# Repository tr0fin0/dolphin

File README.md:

# dolphin
Firmware for `dolphin` board, an ESP32-S3 based sumo robot controller.

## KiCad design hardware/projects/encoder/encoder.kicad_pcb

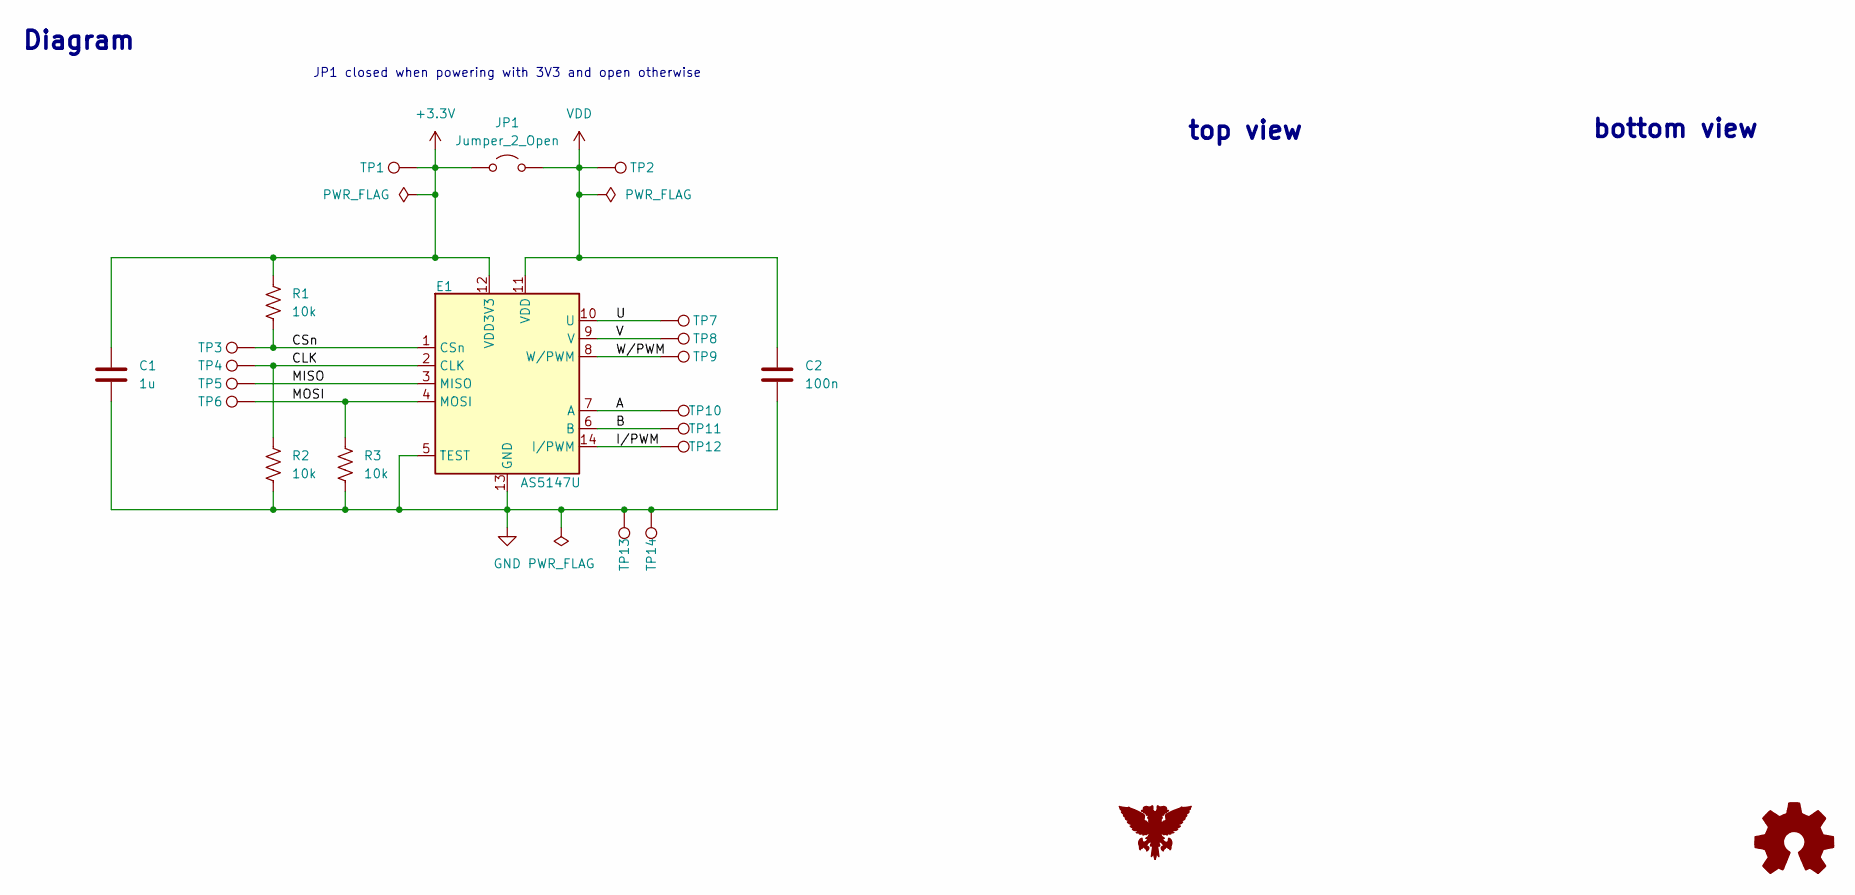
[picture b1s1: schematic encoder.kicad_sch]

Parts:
C1: 1u; C_0805_2012Metric_Pad1.18x1.45mm_HandSolder
C2: 100n; C_0805_2012Metric_Pad1.18x1.45mm_HandSolder
E1: AS5147U; Encoder_AS5147U
JP1: Jumper_2_Open; SolderJumper-2_P1.3mm_Open_TrianglePad1.0x1.5mm
R1, R2, R3: 10k; R_0805_2012Metric_Pad1.20x1.40mm_HandSolder
TP1, TP2, TP3, TP4, TP5, TP6, TP7, TP8, TP9, TP10, TP11, TP12, TP13, TP14: TestPoint; TestPoint_Pad_D1.0mm

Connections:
+3.3V: C1.2, E1.12 (VDD3V3), JP1.1 (A), R1.1, TP1.1 (1_1)
/A: E1.7 (A), TP10.1 (1_1)
/B: E1.6 (B), TP11.1 (1_1)
/CLK: E1.2 (CLK), R2.1, TP4.1 (1_1)
/CSn: E1.1 (CSn), R1.2, TP3.1 (1_1)
/I/PWM: E1.14 (I/PWM), TP12.1 (1_1)
/MISO: E1.3 (MISO), TP5.1 (1_1)
/MOSI: E1.4 (MOSI), R3.1, TP6.1 (1_1)
/U: E1.10 (U), TP7.1 (1_1)
/V: E1.9 (V), TP8.1 (1_1)
/W/PWM: E1.8 (W/PWM), TP9.1 (1_1)
GND: C1.1, C2.1, E1.5 (TEST), E1.13 (GND), R2.2, R3.2, TP13.1 (1_1), TP14.1 (1_1)
VDD: C2.2, E1.11 (VDD), JP1.2 (B), TP2.1 (1_1)

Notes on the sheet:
Diagram
JP1 closed when powering with 3V3 and open otherwise
top view
bottom view

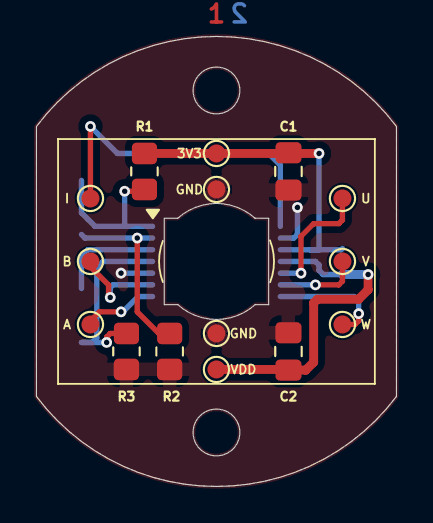
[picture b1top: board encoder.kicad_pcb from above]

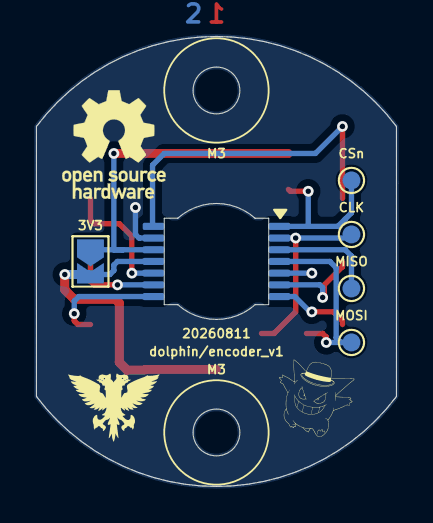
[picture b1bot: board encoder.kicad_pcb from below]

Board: 2 copper layers, 20.0 x 25.0 mm, 21 parts (5 on the bottom side), 13 nets.

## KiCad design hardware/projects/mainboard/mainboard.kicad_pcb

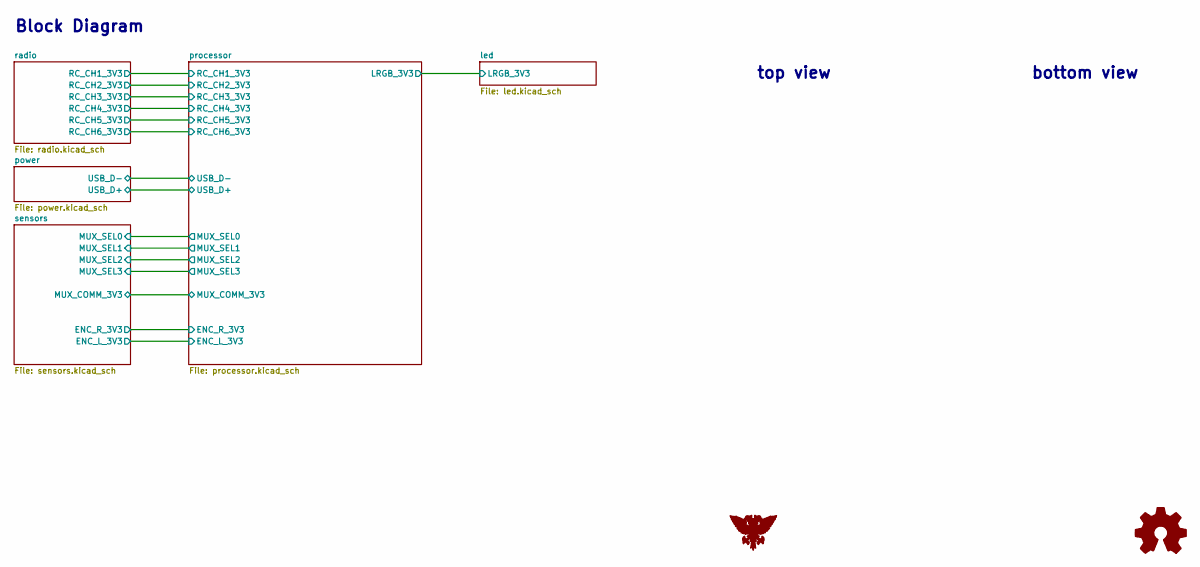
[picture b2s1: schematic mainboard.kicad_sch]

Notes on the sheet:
top view
bottom view
Block Diagram

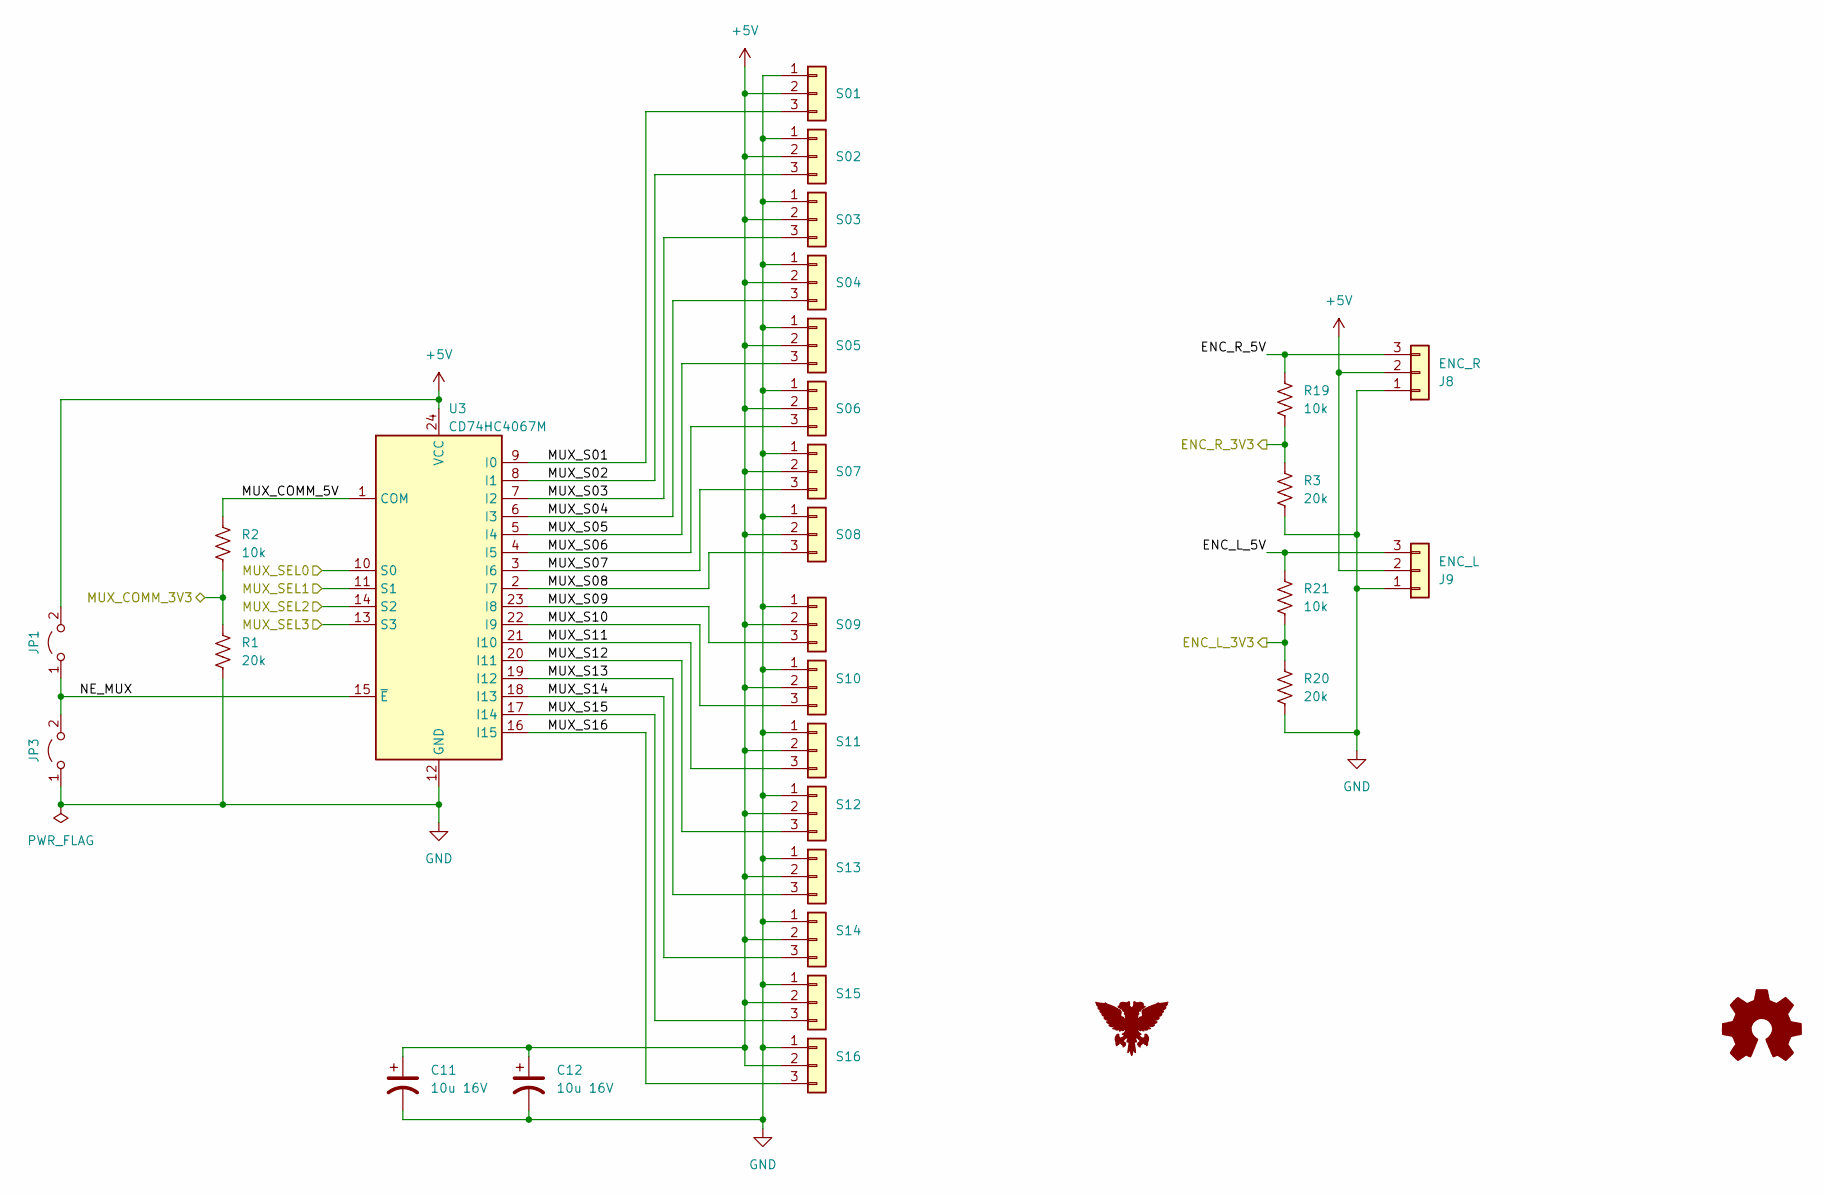
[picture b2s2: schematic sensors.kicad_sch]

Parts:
C11, C12: 10u 16V; CP_Radial_D5.0mm_P2.00mm
J8: ENC_R; Connector_JST_ZH_B3B-ZR_1x03_P1.50mm_Vertical
J9: ENC_L; Connector_JST_ZH_B3B-ZR_1x03_P1.50mm_Vertical
JP1, JP3: Jumper_2_Open; SolderJumper-2_P1.3mm_Open_TrianglePad1.0x1.5mm
R1, R3, R20: 20k; R_0805_2012Metric_Pad1.20x1.40mm_HandSolder
R2, R19, R21: 10k; R_0805_2012Metric_Pad1.20x1.40mm_HandSolder
S01, S02, S03, S04, S05, S06, S07, S08, S09, S10, S11, S12, S13, S14, S15, S16: Conn_01x03; Connector_JST_ZH_B3B-ZR_1x03_P1.50mm_Vertical
U3: CD74HC4067M; SOIC-24W_7.5x15.4mm_P1.27mm

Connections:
+5V: C11.1, C12.1, J8.2, J9.2, JP1.2 (B), S01.2, S02.2, S03.2, S04.2, S05.2, S06.2, S07.2, S08.2, S09.2, S10.2, S11.2, S12.2, S13.2, S14.2, S15.2, S16.2, U3.24 (VCC); also elsewhere on the board
/processor/ENC_L_3V3: R20.1, R21.1; also elsewhere on the board
/processor/ENC_R_3V3: R3.1, R19.1; also elsewhere on the board
/processor/MUX_COMM_3V3: R1.1, R2.1; also elsewhere on the board
/processor/MUX_SEL0: U3.10 (S0); also elsewhere on the board
/processor/MUX_SEL1: U3.11 (S1); also elsewhere on the board
/processor/MUX_SEL2: U3.14 (S2); also elsewhere on the board
/processor/MUX_SEL3: U3.13 (S3); also elsewhere on the board
/sensors/ENC_L_5V: J9.3, R21.2
/sensors/ENC_R_5V: J8.3, R19.2
/sensors/MUX_COMM_5V: R2.2, U3.1 (COM)
/sensors/MUX_S01: S01.3, U3.9 (I0)
/sensors/MUX_S02: S02.3, U3.8 (I1)
/sensors/MUX_S03: S03.3, U3.7 (I2)
/sensors/MUX_S04: S04.3, U3.6 (I3)
/sensors/MUX_S05: S05.3, U3.5 (I4)
/sensors/MUX_S06: S06.3, U3.4 (I5)
/sensors/MUX_S07: S07.3, U3.3 (I6)
/sensors/MUX_S08: S08.3, U3.2 (I7)
/sensors/MUX_S09: S09.3, U3.23 (I8)
/sensors/MUX_S10: S10.3, U3.22 (I9)
/sensors/MUX_S11: S11.3, U3.21 (I10)
/sensors/MUX_S12: S12.3, U3.20 (I11)
/sensors/MUX_S13: S13.3, U3.19 (I12)
/sensors/MUX_S14: S14.3, U3.18 (I13)
/sensors/MUX_S15: S15.3, U3.17 (I14)
/sensors/MUX_S16: S16.3, U3.16 (I15)
/sensors/NE_MUX: JP1.1 (A), JP3.2 (B), U3.15 (~E)
GND: C11.2, C12.2, J8.1, J9.1, JP3.1 (A), R1.2, R3.2, R20.2, S01.1, S02.1, S03.1, S04.1, S05.1, S06.1, S07.1, S08.1, S09.1, S10.1, S11.1, S12.1, S13.1, S14.1, S15.1, S16.1, U3.12 (GND); also elsewhere on the board

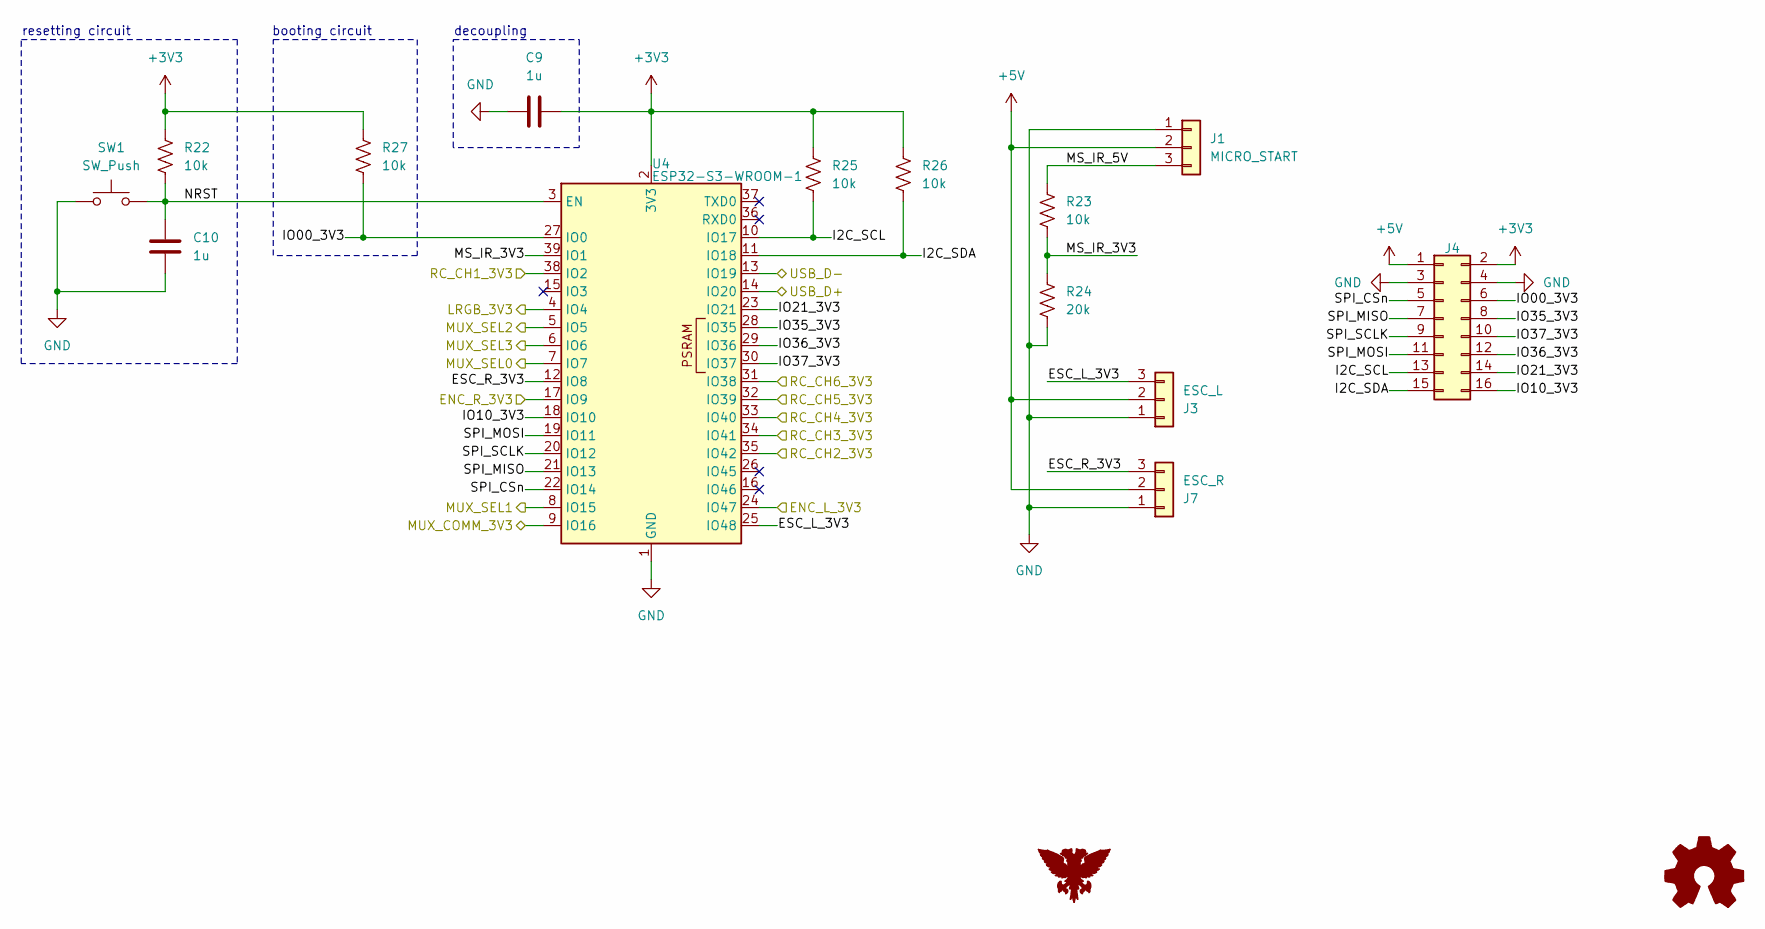
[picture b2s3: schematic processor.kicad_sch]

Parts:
C9, C10: 1u; C_0805_2012Metric_Pad1.18x1.45mm_HandSolder
J1: MICRO_START; Connector_JST_ZH_B3B-ZR_1x03_P1.50mm_Vertical
J3: ESC_L; PinSocket_1x03_P2.54mm_Vertical
J4: Conn_02x08_Odd_Even; PinSocket_2x08_P2.54mm_Vertical
J7: ESC_R; PinSocket_1x03_P2.54mm_Vertical
R22, R23, R25, R26, R27: 10k; R_0805_2012Metric_Pad1.20x1.40mm_HandSolder
R24: 20k; R_0805_2012Metric_Pad1.20x1.40mm_HandSolder
SW1: SW_Push; SW_SPST_PTS810
U4: ESP32-S3-WROOM-1

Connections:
+3V3: C9.2, J4.2, R22.1, R25.1, R26.1, R27.2, U4.2 (3V3); also elsewhere on the board
+5V: J1.2, J3.2, J4.1, J7.2; also elsewhere on the board
/led/LRGB_3V3: U4.4 (IO4); also elsewhere on the board
/power/USB_D+: U4.14 (IO20); also elsewhere on the board
/power/USB_D-: U4.13 (IO19); also elsewhere on the board
/processor/ENC_L_3V3: U4.24 (IO47); also elsewhere on the board
/processor/ENC_R_3V3: U4.17 (IO9); also elsewhere on the board
/processor/ESC_L_3V3: J3.3, U4.25 (IO48)
/processor/ESC_R_3V3: J7.3, U4.12 (IO8)
/processor/I2C_SCL: J4.13, R25.2, U4.10 (IO17)
/processor/I2C_SDA: J4.15, R26.2, U4.11 (IO18)
/processor/IO00_3V3: J4.6, R27.1, U4.27 (IO0)
/processor/IO10_3V3: J4.16, U4.18 (IO10)
/processor/IO21_3V3: J4.14, U4.23 (IO21)
/processor/IO35_3V3: J4.8, U4.28 (IO35)
/processor/IO36_3V3: J4.12, U4.29 (IO36)
/processor/IO37_3V3: J4.10, U4.30 (IO37)
/processor/MS_IR_3V3: R23.2, R24.1, U4.39 (IO1)
/processor/MS_IR_5V: J1.3, R23.1
/processor/MUX_COMM_3V3: U4.9 (IO16); also elsewhere on the board
/processor/MUX_SEL0: U4.7 (IO7); also elsewhere on the board
/processor/MUX_SEL1: U4.8 (IO15); also elsewhere on the board
/processor/MUX_SEL2: U4.5 (IO5); also elsewhere on the board
/processor/MUX_SEL3: U4.6 (IO6); also elsewhere on the board
/processor/NRST: C10.1, R22.2, SW1.2, U4.3 (EN)
/processor/RC_CH1_3V3: U4.38 (IO2); also elsewhere on the board
/processor/RC_CH2_3V3: U4.35 (IO42); also elsewhere on the board
/processor/RC_CH3_3V3: U4.34 (IO41); also elsewhere on the board
/processor/RC_CH4_3V3: U4.33 (IO40); also elsewhere on the board
/processor/RC_CH5_3V3: U4.32 (IO39); also elsewhere on the board
/processor/RC_CH6_3V3: U4.31 (IO38); also elsewhere on the board
/processor/SPI_CSn: J4.5, U4.22 (IO14)
/processor/SPI_MISO: J4.7, U4.21 (IO13)
/processor/SPI_MOSI: J4.11, U4.19 (IO11)
/processor/SPI_SCLK: J4.9, U4.20 (IO12)
GND: C9.1, C10.2, J1.1, J3.1, J4.3, J4.4, J7.1, R24.2, SW1.1, U4.1 (GND), U4.40 (GND), U4.41 (GND); also elsewhere on the board

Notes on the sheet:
resetting circuit
decoupling
booting circuit

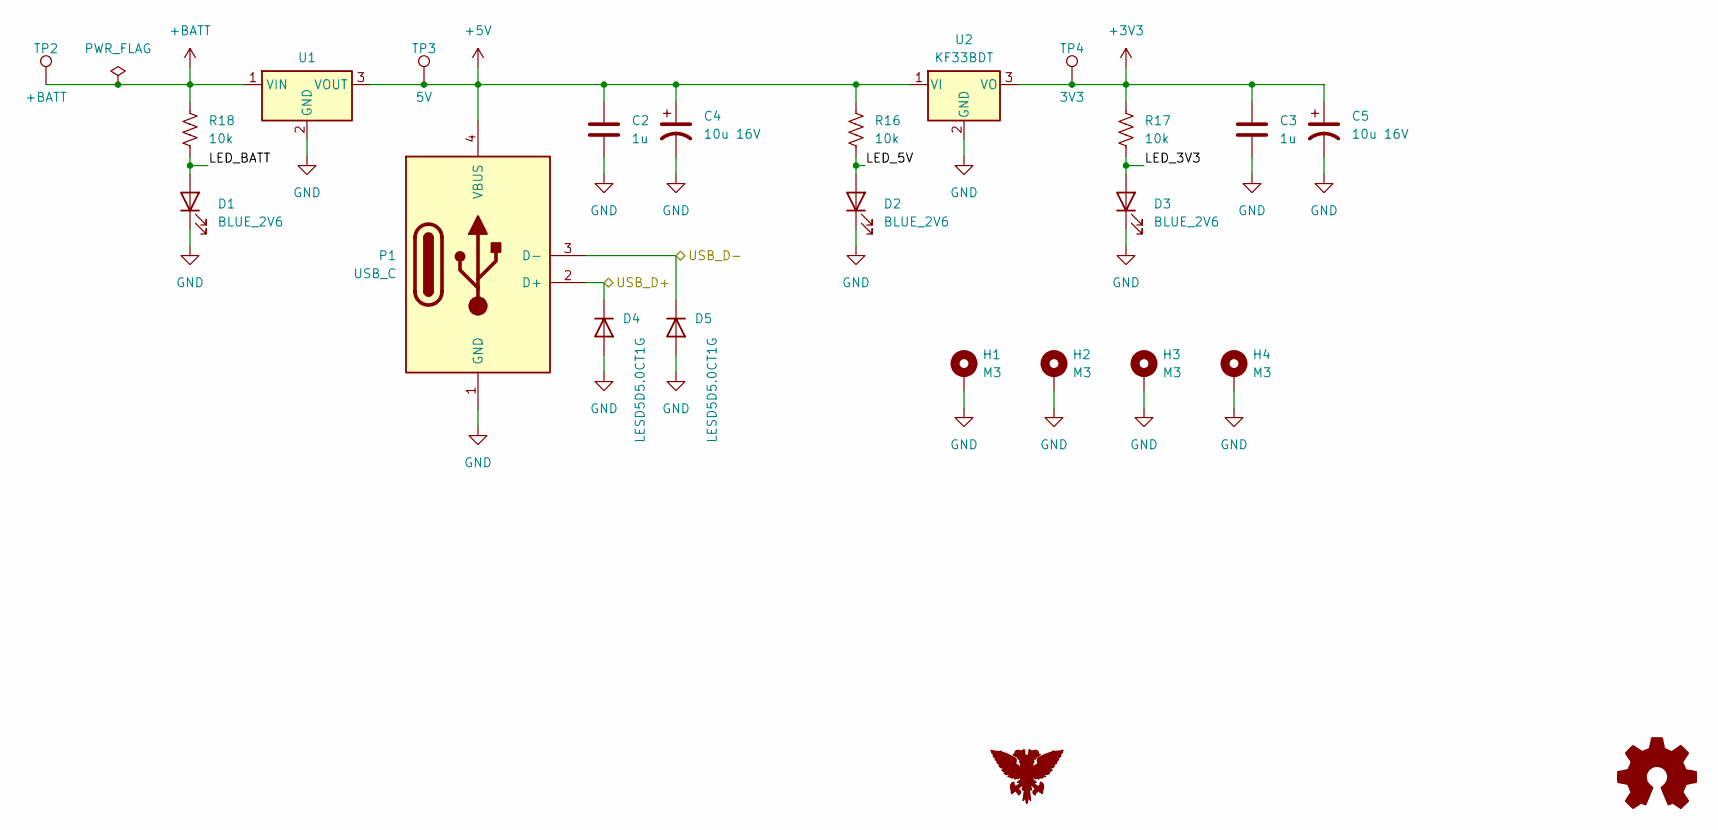
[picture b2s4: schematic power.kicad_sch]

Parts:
C2, C3: 1u; C_0805_2012Metric_Pad1.18x1.45mm_HandSolder
C4, C5: 10u 16V; CP_Radial_D5.0mm_P2.00mm
D1, D2, D3: BLUE_2V6; LED_0805_2012Metric_Pad1.15x1.40mm_HandSolder
D4, D5: LESD5D5.0CT1G; D_0805_2012Metric_Pad1.15x1.40mm_HandSolder
H1, H2, H3, H4: M3; MountingHole_3.2mm_M3_Pad_Via
P1: USB_C; Connector_USB-C
R16, R17, R18: 10k; R_0805_2012Metric_Pad1.20x1.40mm_HandSolder
TP2: +BATT; TestPoint_Pad_D1.0mm
TP3: 5V; TestPoint_Pad_D1.0mm
TP4: 3V3; TestPoint_Pad_D1.0mm
U1: Regulator_DC-DC_MINI-360
U2: KF33BDT; Regulator_KF33BD-TR

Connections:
+3V3: C3.1, C5.1, R17.1, TP4.1 (1_1), U2.3 (VO); also elsewhere on the board
+5V: C2.1, C4.1, P1.4 (VBUS), R16.1, TP3.1 (1_1), U1.3 (VOUT), U2.1 (VI); also elsewhere on the board
+BATT: R18.1, TP2.1 (1_1), U1.1 (VIN)
/power/LED_3V3: D3.2 (A), R17.2
/power/LED_5V: D2.2 (A), R16.2
/power/LED_BATT: D1.2 (A), R18.2
/power/USB_D+: D4.1 (K), P1.2 (D+); also elsewhere on the board
/power/USB_D-: D5.1 (K), P1.3 (D-); also elsewhere on the board
GND: C2.2, C3.2, C4.2, C5.2, D1.1 (K), D2.1 (K), D3.1 (K), D4.2 (A), D5.2 (A), H1.1 (1_1), H2.1 (1_1), H3.1 (1_1), H4.1 (1_1), P1.1 (GND), U1.2 (GND), U2.2 (GND); also elsewhere on the board

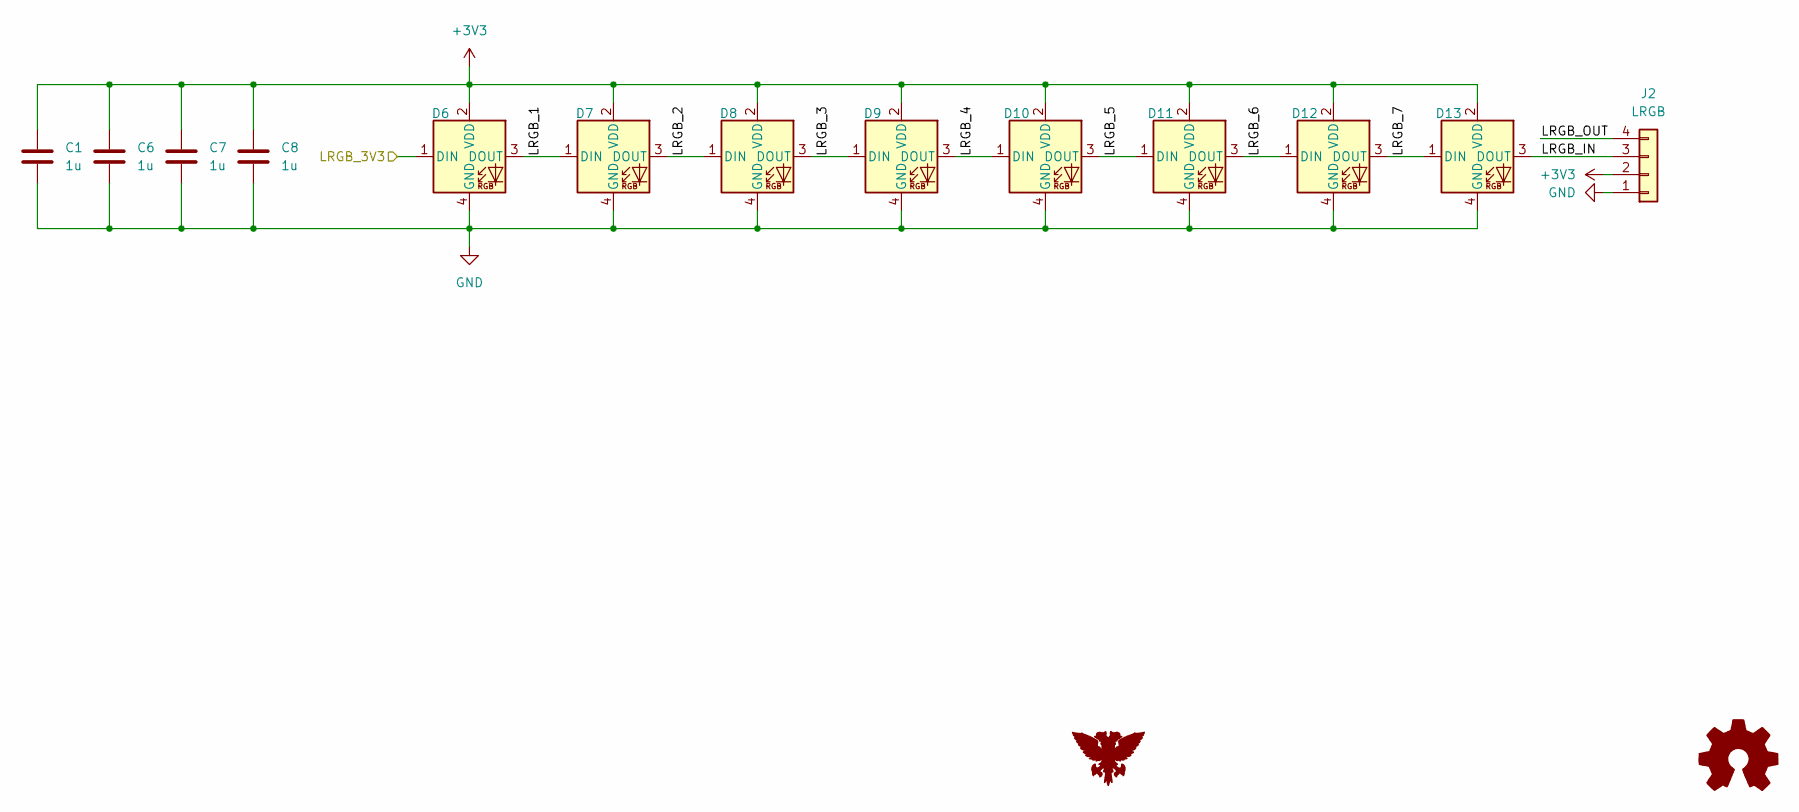
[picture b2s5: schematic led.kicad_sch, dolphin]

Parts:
C1, C6, C7, C8: 1u; C_0805_2012Metric_Pad1.18x1.45mm_HandSolder
D6, D7, D8, D9, D10, D11, D12, D13: WS2812B-4020-G1; LED_WS2812B-4020
J2: LRGB; Connector_JST_ZH_B4B-ZR_1x04_P1.50mm_Vertical

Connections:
+3V3: C1.1, C6.1, C7.1, C8.1, D6.2 (VDD), D7.2 (VDD), D8.2 (VDD), D9.2 (VDD), D10.2 (VDD), D11.2 (VDD), D12.2 (VDD), D13.2 (VDD), J2.2; also elsewhere on the board
/led/LRGB_1: D6.3 (DOUT), D7.1 (DIN)
/led/LRGB_2: D7.3 (DOUT), D8.1 (DIN)
/led/LRGB_3: D8.3 (DOUT), D9.1 (DIN)
/led/LRGB_3V3: D6.1 (DIN); also elsewhere on the board
/led/LRGB_4: D9.3 (DOUT), D10.1 (DIN)
/led/LRGB_5: D10.3 (DOUT), D11.1 (DIN)
/led/LRGB_6: D11.3 (DOUT), D12.1 (DIN)
/led/LRGB_7: D12.3 (DOUT), D13.1 (DIN)
/led/LRGB_IN: D13.3 (DOUT), J2.3
/led/LRGB_OUT: J2.4
GND: C1.2, C6.2, C7.2, C8.2, D6.4 (GND), D7.4 (GND), D8.4 (GND), D9.4 (GND), D10.4 (GND), D11.4 (GND), D12.4 (GND), D13.4 (GND), J2.1; also elsewhere on the board

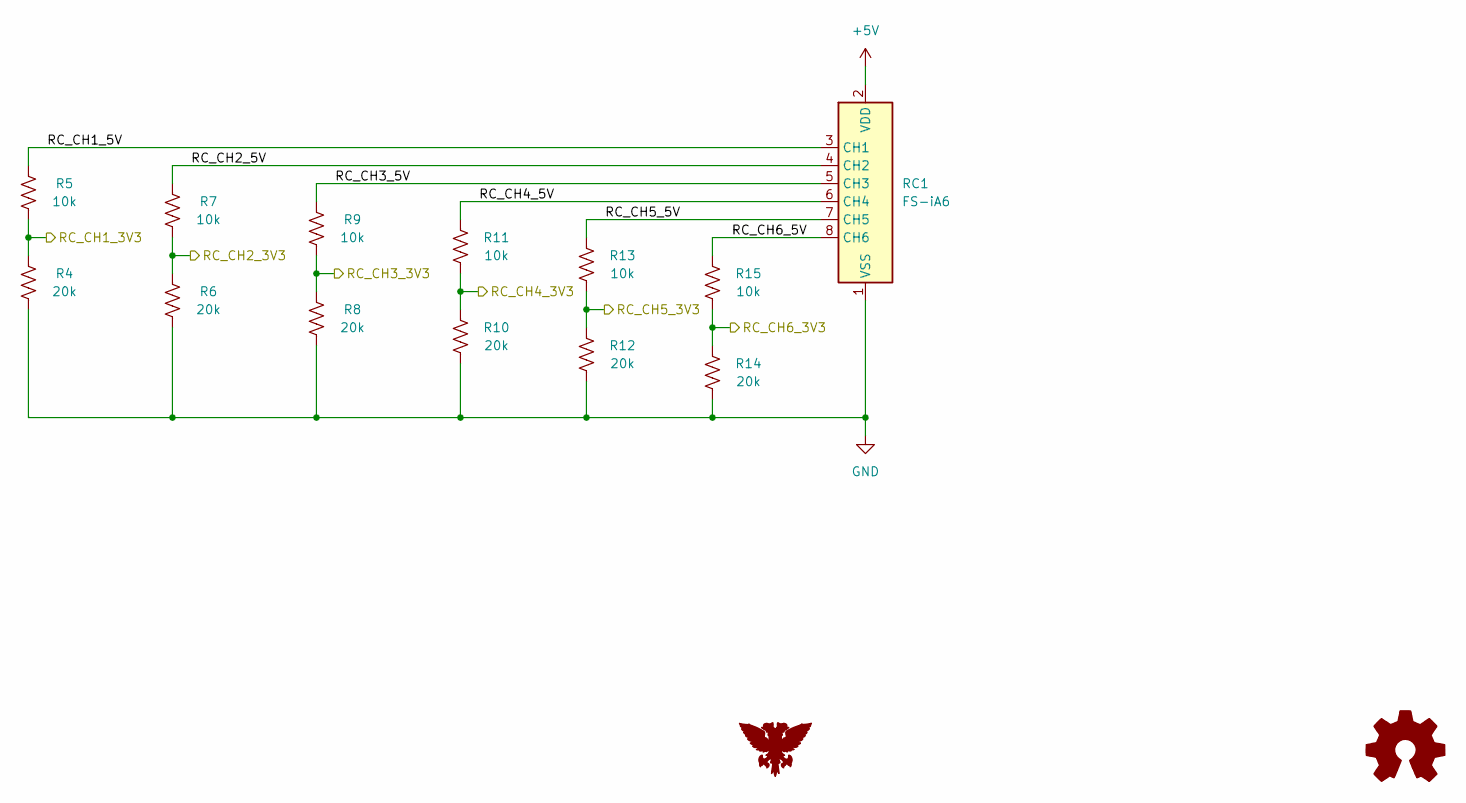
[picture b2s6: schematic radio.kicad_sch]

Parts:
R4, R6, R8, R10, R12, R14: 20k; R_0805_2012Metric_Pad1.20x1.40mm_HandSolder
R5, R7, R9, R11, R13, R15: 10k; R_0805_2012Metric_Pad1.20x1.40mm_HandSolder
RC1: FS-iA6; Receiver_FS-iA6

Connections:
+5V: RC1.2 (VDD); also elsewhere on the board
/processor/RC_CH1_3V3: R4.2, R5.1; also elsewhere on the board
/processor/RC_CH2_3V3: R6.2, R7.1; also elsewhere on the board
/processor/RC_CH3_3V3: R8.2, R9.1; also elsewhere on the board
/processor/RC_CH4_3V3: R10.2, R11.1; also elsewhere on the board
/processor/RC_CH5_3V3: R12.2, R13.1; also elsewhere on the board
/processor/RC_CH6_3V3: R14.2, R15.1; also elsewhere on the board
/radio/RC_CH1_5V: R5.2, RC1.3 (CH1)
/radio/RC_CH2_5V: R7.2, RC1.4 (CH2)
/radio/RC_CH3_5V: R9.2, RC1.5 (CH3)
/radio/RC_CH4_5V: R11.2, RC1.6 (CH4)
/radio/RC_CH5_5V: R13.2, RC1.7 (CH5)
/radio/RC_CH6_5V: R15.2, RC1.8 (CH6)
GND: R4.1, R6.1, R8.1, R10.1, R12.1, R14.1, RC1.1 (VSS); also elsewhere on the board

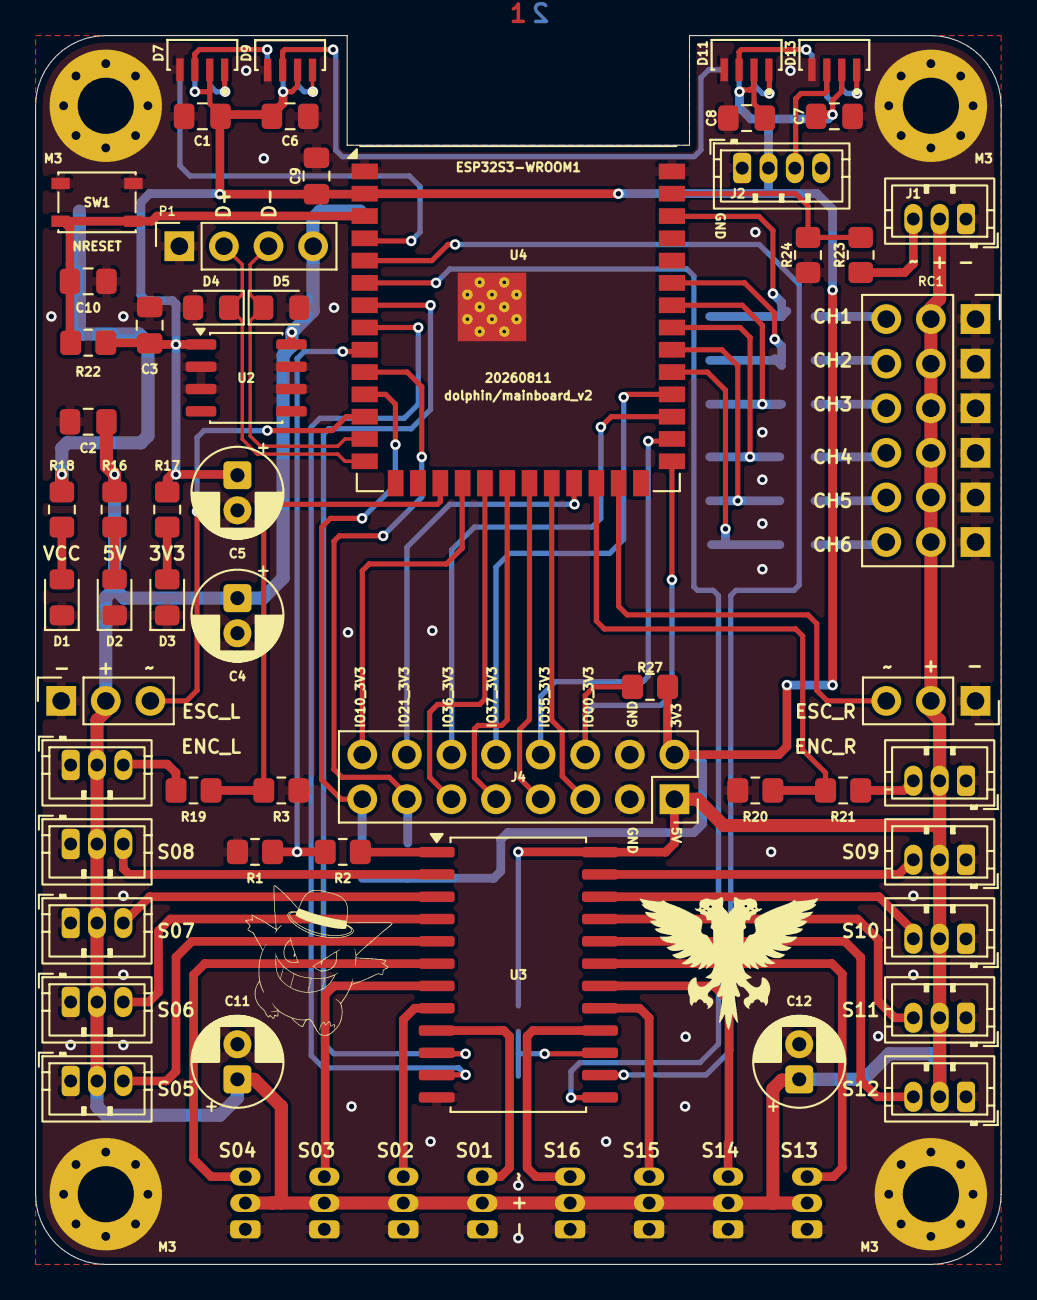
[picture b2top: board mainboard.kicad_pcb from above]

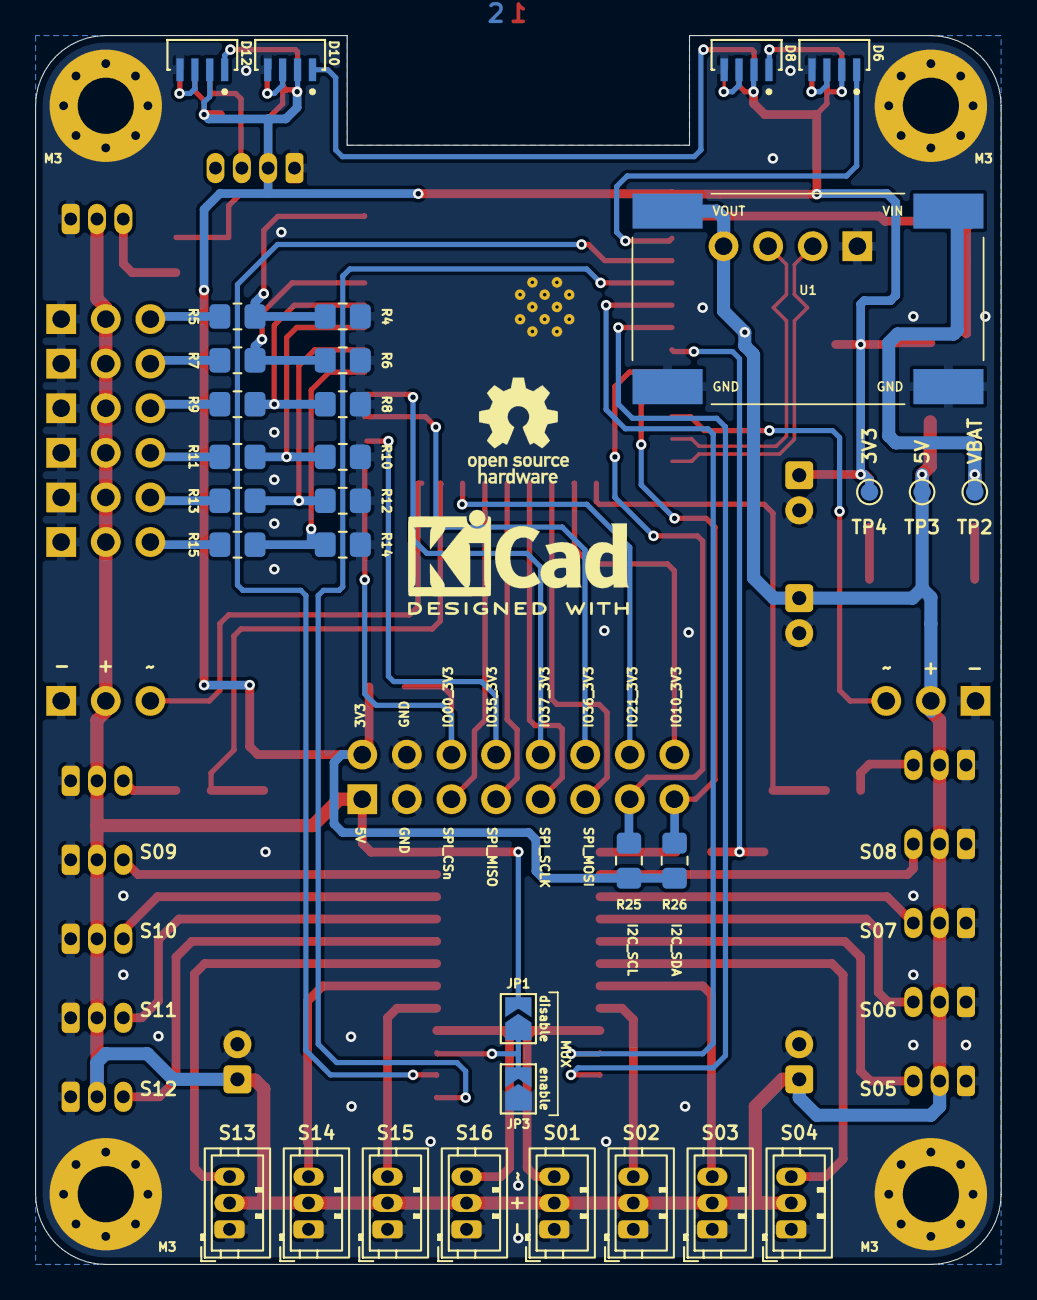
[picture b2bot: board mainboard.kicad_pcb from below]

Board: 2 copper layers, 55.0 x 70.0 mm, 91 parts (32 on the bottom side), 74 nets.

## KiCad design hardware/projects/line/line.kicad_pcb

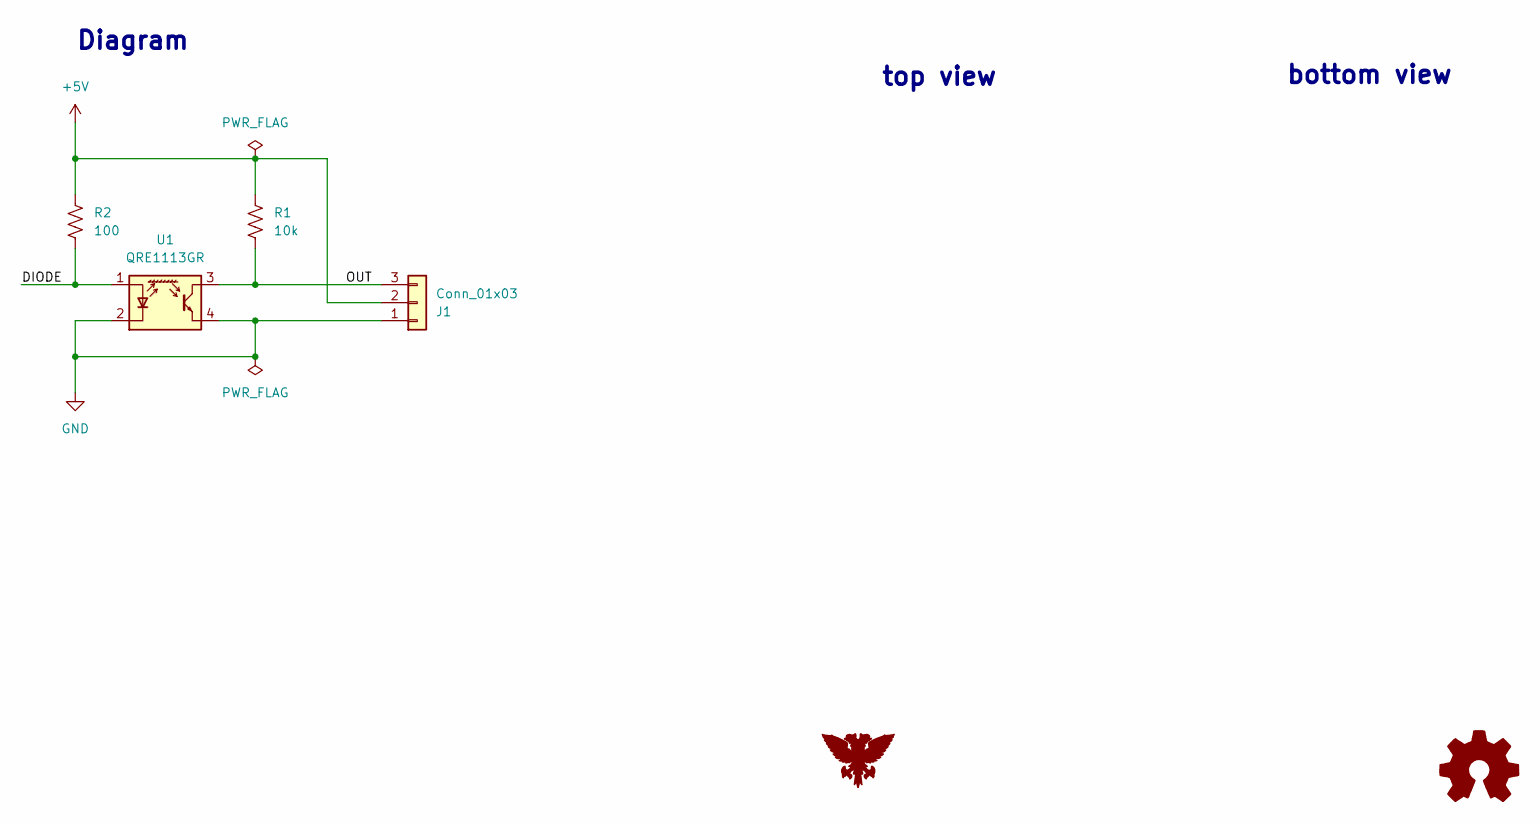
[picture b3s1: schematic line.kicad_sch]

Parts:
J1: Conn_01x03; PinHeader_1x03_P2.54mm_Vertical
R1: 10k; R_0805_2012Metric_Pad1.20x1.40mm_HandSolder
R2: 100; R_0805_2012Metric_Pad1.20x1.40mm_HandSolder
U1: QRE1113GR; OnSemi_CASE100CY

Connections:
+5V: J1.2, R1.1, R2.1
/DIODE: R2.2, U1.1 (A)
/OUT: J1.3, R1.2, U1.3
GND: J1.1, U1.2 (K), U1.4

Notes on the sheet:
bottom view
top view
Diagram

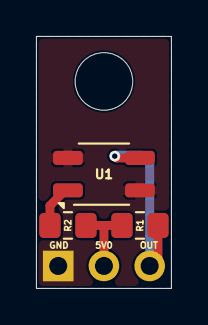
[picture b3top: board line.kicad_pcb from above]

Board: 2 copper layers, 7.5 x 14.0 mm, 4 parts (0 on the bottom side), 4 nets.

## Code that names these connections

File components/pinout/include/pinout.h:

/**
 * @file pinout.h
 * @brief Mainboard pinout.
 *
 * @author Guilherme Nunes Trofino
 * @date 2026-04-26
 */

#pragma once

#include "config.h"
#include <stdint.h>

/**
 * @brief Physical connection on the mainboard board.
 */
typedef enum pin {
#ifdef CONFIG_MAINBOARD_V2
    PIN_ENC_L = 47,         /**< ``GPIO 47`` : @ref ENCODER_L connection. */
    PIN_ENC_R = 9,          /**< ``GPIO 09`` : @ref ENCODER_R connection. */
    PIN_ESC_L = 48,         /**< ``GPIO 48`` : @ref ESC_L connection. */
    PIN_ESC_R = 8,          /**< ``GPIO 08`` : @ref ESC_R connection. */
    PIN_I2C_SCL = 17,       /**< ``GPIO 17`` : I2C clock line connection. */
    PIN_I2C_SDA = 18,       /**< ``GPIO 18`` : I2C data line connection. */
    PIN_IO00 = 0,           /**< ``GPIO 00`` : actively low, enables ESP32 boot mode. */
    PIN_IO10 = 10,          /**< ``GPIO 10`` : spare connection. */
    PIN_IO21 = 21,          /**< ``GPIO 21`` : spare connection. */
    PIN_IO35 = 35,          /**< ``GPIO 35`` : spare connection. */
    PIN_IO36 = 36,          /**< ``GPIO 36`` : spare connection. */
    PIN_IO37 = 37,          /**< ``GPIO 37`` : spare connection. */
    PIN_IRR = 1,            /**< ``GPIO 01`` : @ref ir_t infrared receiver connection. */
    PIN_LRGB = 4,           /**< ``GPIO 04`` : @ref led_array_t pin connection. */
    PIN_MUX_COMMON = 16,    /**< ``GPIO 16`` : @ref mux_t common pin connection. */
    PIN_MUX_ADDR0 = 7,      /**< ``GPIO 07`` : @ref mux_t address pin 0 connection. */
    PIN_MUX_ADDR1 = 15,     /**< ``GPIO 15`` : @ref mux_t address pin 1 connection. */
    PIN_MUX_ADDR2 = 5,      /**< ``GPIO 05`` : @ref mux_t address pin 2 connection. */
    PIN_MUX_ADDR3 = 6,      /**< ``GPIO 06`` : @ref mux_t address pin 3 connection. */
    PIN_RC_CH1 = 2,         /**< ``GPIO 02`` : @ref RADIO_CHANNEL_1 connection. */
    PIN_RC_CH2 = 42,        /**< ``GPIO 42`` : @ref RADIO_CHANNEL_2 connection. */
    PIN_RC_CH3 = 41,        /**< ``GPIO 41`` : @ref RADIO_CHANNEL_3 connection. */
    PIN_RC_CH4 = 40,        /**< ``GPIO 40`` : @ref RADIO_CHANNEL_4 connection. */
    PIN_RC_CH5 = 39,        /**< ``GPIO 39`` : @ref RADIO_CHANNEL_5 connection. */
    PIN_RC_CH6 = 38,        /**< ``GPIO 38`` : @ref RADIO_CHANNEL_6 connection. */
    PIN_SPI_MISO = 13,      /**< ``GPIO 13`` : SPI Master In Slave Out connection. */
    PIN_SPI_MOSI = 11,      /**< ``GPIO 11`` : SPI Master Out Slave In connection. */
    PIN_SPI_SCLK = 12,      /**< ``GPIO 12`` : SPI clock connection. */
    NUMBER_OF_PINS = 28     /**< Number of pin connections. */
#elifdef CONFIG_MAINBOARD_V1
    PIN_BUTTON_BOOT = 0,    /**< ``GPIO 00`` : BOOT connection. */
    PIN_ENC_L = 10,         /**< ``GPIO 10`` : @ref ENCODER_L connection A. */
    PIN_ENCODER_L_B = 21,   /**< ``GPIO 21`` : @ref ENCODER_L connection B. */
    PIN_ENCODER_L_CS = 48,  /**< ``GPIO 48`` : @ref ENCODER_L connection CS. */
    PIN_ENC_R = 9,          /**< ``GPIO 09`` : @ref ENCODER_R connection A. */
    PIN_ENCODER_R_B = 14,   /**< ``GPIO 14`` : @ref ENCODER_R connection B. */
    PIN_ENCODER_R_CS = 47,  /**< ``GPIO 47`` : @ref ENCODER_R connection CS. */
    PIN_ESC_L = 2,          /**< ``GPIO 02`` : @ref ESC_L connection. */
    PIN_ESC_R = 1,          /**< ``GPIO 01`` : @ref ESC_R connection. */
    PIN_I2C_SCL = 17,       /**< ``GPIO 17`` : I2C clock line connection. */
    PIN_I2C_SDA = 18,       /**< ``GPIO 18`` : I2C data line connection. */
    PIN_IRR = 35,           /**< ``GPIO 35`` : @ref ir_t infrared receiver connection. */
    PIN_RC_CH1 = 42,        /**< ``GPIO 42`` : @ref RADIO_CHANNEL_1 connection. */
    PIN_RC_CH2 = 41,        /**< ``GPIO 41`` : @ref RADIO_CHANNEL_2 connection. */
    PIN_RC_CH3 = 40,        /**< ``GPIO 40`` : @ref RADIO_CHANNEL_3 connection. */
    PIN_RC_CH4 = 39,        /**< ``GPIO 39`` : @ref RADIO_CHANNEL_4 connection. */
    PIN_RC_CH5 = 38,        /**< ``GPIO 38`` : @ref RADIO_CHANNEL_5 connection. */
    PIN_RC_CH6 = 37,        /**< ``GPIO 37`` : @ref RADIO_CHANNEL_6 connection. */
    PIN_LRGB = 8,           /**< ``GPIO 08`` : @ref led_array_t pin connection. */
    PIN_SPARE = 36,         /**< ``GPIO 36`` : spare connection. */
    PIN_SPI_MISO = 13,      /**< ``GPIO 13`` : SPI Master In Slave Out connection. */
    PIN_SPI_MOSI = 11,      /**< ``GPIO 11`` : SPI Master Out Slave In connection. */
    PIN_SPI_SCLK = 12,      /**< ``GPIO 12`` : SPI clock connection. */
    PIN_MUX_COMMON = 7,     /**< ``GPIO 07`` : @ref mux_t common pin connection. */
    PIN_MUX_ENABLE = 4,     /**< ``GPIO 04`` : @ref mux_t enable pin connection. */
    PIN_MUX_ADDR0 = 15,     /**< ``GPIO 15`` : @ref mux_t address pin 0 connection. */
    PIN_MUX_ADDR1 = 16,     /**< ``GPIO 16`` : @ref mux_t address pin 1 connection. */
    PIN_MUX_ADDR2 = 5,      /**< ``GPIO 05`` : @ref mux_t address pin 2 connection. */
    PIN_MUX_ADDR3 = 6,      /**< ``GPIO 06`` : @ref mux_t address pin 3 connection. */
    NUMBER_OF_PINS = 29     /**< Number of pin connections. */
#endif
} pin_t;
